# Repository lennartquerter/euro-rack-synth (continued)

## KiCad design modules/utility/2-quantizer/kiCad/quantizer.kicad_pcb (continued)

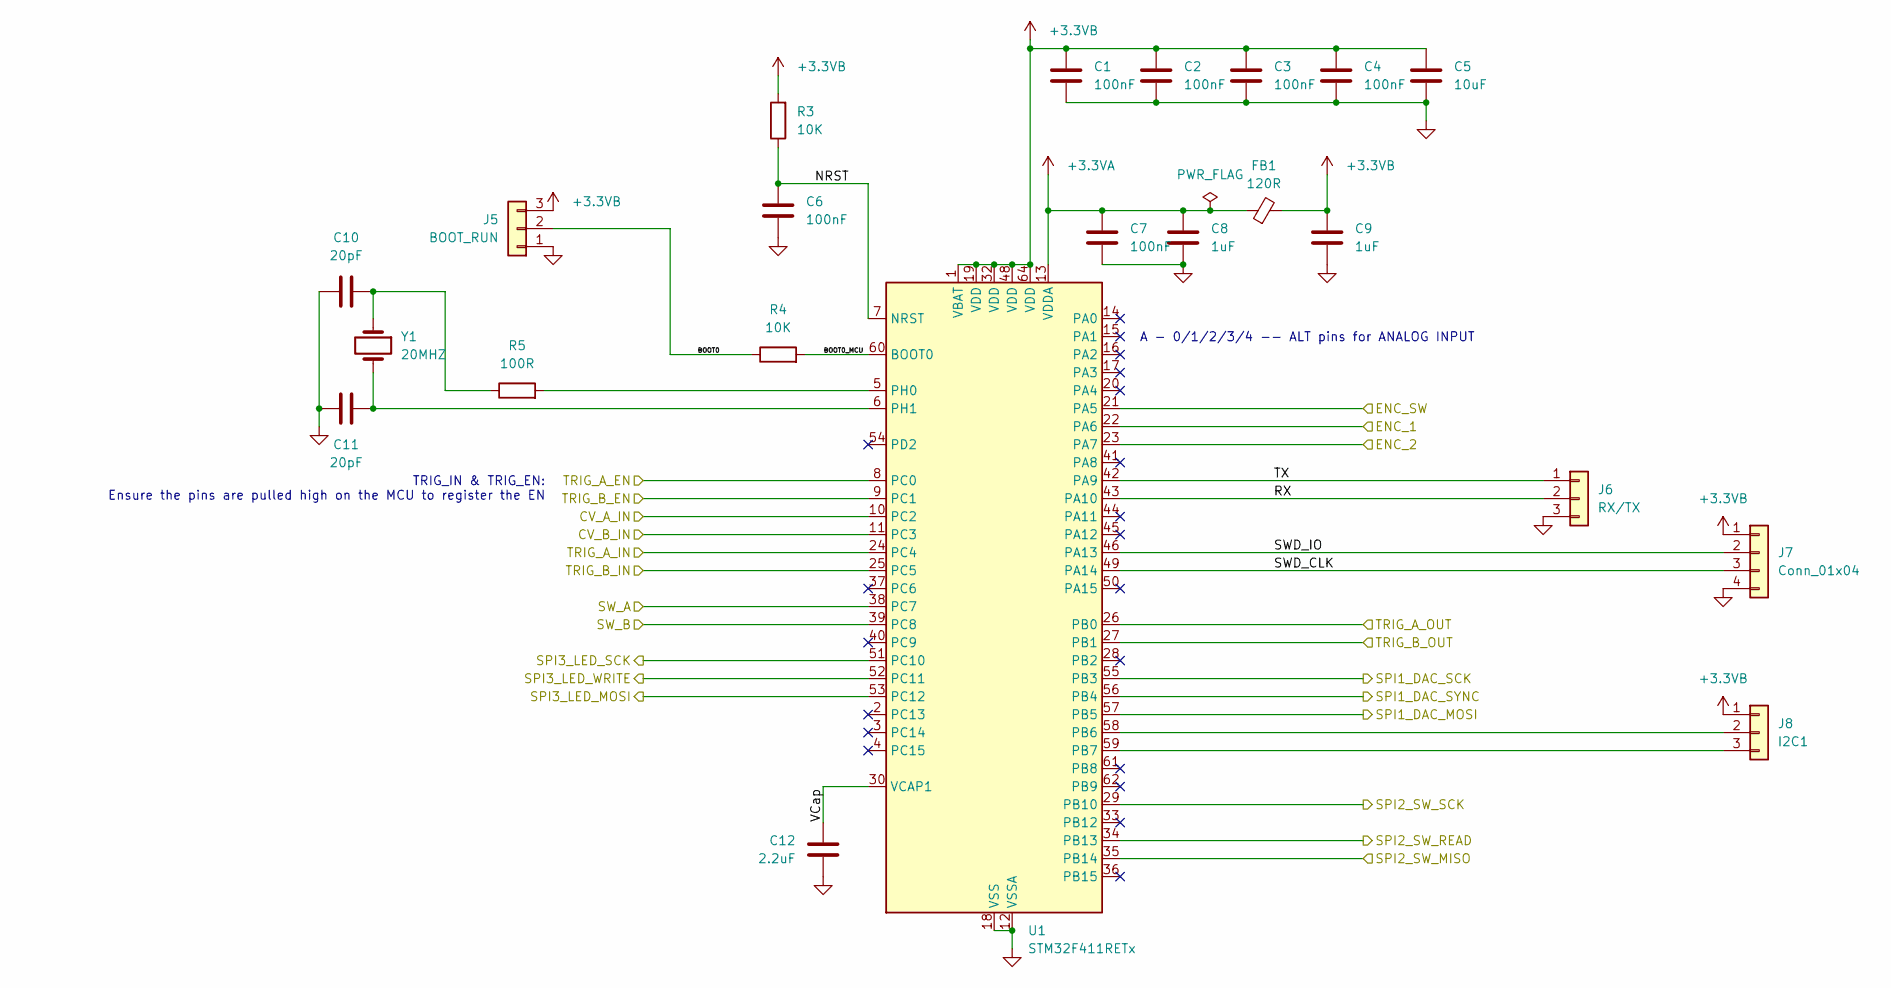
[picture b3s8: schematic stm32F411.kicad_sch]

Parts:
C1, C2, C3, C4, C6, C7: 100nF; C_0805_2012Metric_Pad1.18x1.45mm_HandSolder
C5: 10uF; C_0805_2012Metric_Pad1.18x1.45mm_HandSolder
C8, C9: 1uF; C_0805_2012Metric_Pad1.18x1.45mm_HandSolder
C10, C11: 20pF; C_0805_2012Metric_Pad1.18x1.45mm_HandSolder
C12: 2.2uF; C_0805_2012Metric_Pad1.18x1.45mm_HandSolder
FB1: 120R; L_0805_2012Metric_Pad1.05x1.20mm_HandSolder
J5: BOOT_RUN; PinHeader_1x03_P2.54mm_Vertical
J6: RX/TX; PinHeader_1x03_P2.54mm_Vertical
J7: Conn_01x04; PinHeader_1x04_P2.54mm_Vertical
J8: I2C1; PinHeader_1x03_P2.54mm_Vertical
R3, R4: 10K; R_0805_2012Metric_Pad1.20x1.40mm_HandSolder
R5: 100R; R_0805_2012Metric_Pad1.20x1.40mm_HandSolder
U1: STM32F411RETx; LQFP-64_10x10mm_P0.5mm
Y1: 20MHZ; Crystal_SMD_HC49-SD

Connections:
+3.3VA: C7.2, C8.2, FB1.1, U1.13 (VDDA)
+3.3VB: C1.2, C2.2, C3.2, C4.2, C5.2, C9.2, FB1.2, J5.3, J7.1, J8.1, R3.2, U1.1 (VBAT), U1.19 (VDD), U1.32 (VDD), U1.48 (VDD), U1.64 (VDD); also elsewhere on the board
/cv_normalizer1/CV_OUT: U1.11 (PC3); also elsewhere on the board
/cv_normalizer/CV_OUT: U1.10 (PC2); also elsewhere on the board
/cv_output/SCLK: U1.55 (PB3); also elsewhere on the board
/cv_output/SDIN: U1.57 (PB5); also elsewhere on the board
/cv_output/_SYNC: U1.56 (PB4); also elsewhere on the board
/stm32F411/BOOT0: J5.2, R4.1
/stm32F411/BOOT0_MCU: R4.2, U1.60 (BOOT0)
/stm32F411/ENC_1: U1.22 (PA6); also elsewhere on the board
/stm32F411/ENC_2: U1.23 (PA7); also elsewhere on the board
/stm32F411/ENC_SW: U1.21 (PA5); also elsewhere on the board
/stm32F411/NRST: C6.1, R3.1, U1.7 (NRST)
/stm32F411/RX: J6.2, U1.43 (PA10)
/stm32F411/SPI2_SW_MISO: U1.35 (PB14); also elsewhere on the board
/stm32F411/SPI2_SW_READ: U1.34 (PB13); also elsewhere on the board
/stm32F411/SPI2_SW_SCK: U1.29 (PB10); also elsewhere on the board
/stm32F411/SPI3_LED_MOSI: U1.53 (PC12); also elsewhere on the board
/stm32F411/SPI3_LED_SCK: U1.51 (PC10); also elsewhere on the board
/stm32F411/SPI3_LED_WRITE: U1.52 (PC11); also elsewhere on the board
/stm32F411/SWD_CLK: J7.3, U1.49 (PA14)
/stm32F411/SWD_IO: J7.2, U1.46 (PA13)
/stm32F411/SW_A: U1.38 (PC7); also elsewhere on the board
/stm32F411/SW_B: U1.39 (PC8); also elsewhere on the board
/stm32F411/TRIG_A_EN: U1.8 (PC0); also elsewhere on the board
/stm32F411/TRIG_A_IN: U1.24 (PC4); also elsewhere on the board
/stm32F411/TRIG_A_OUT: U1.26 (PB0); also elsewhere on the board
/stm32F411/TRIG_B_EN: U1.9 (PC1); also elsewhere on the board
/stm32F411/TRIG_B_IN: U1.25 (PC5); also elsewhere on the board
/stm32F411/TRIG_B_OUT: U1.27 (PB1); also elsewhere on the board
/stm32F411/TX: J6.1, U1.42 (PA9)
/stm32F411/VCap: C12.1, U1.30 (VCAP1)
GND: C1.1, C2.1, C3.1, C4.1, C5.1, C6.2, C7.1, C8.1, C9.1, C10.2, C11.2, C12.2, J5.1, J6.3, J7.4, U1.12 (VSSA), U1.18 (VSS), U1.31 (VSS), U1.47 (VSS), U1.63 (VSS); also elsewhere on the board
unnamed: C10.1, R5.1, Y1.1
unnamed: J8.2, U1.58 (PB6)
unnamed: J8.3, U1.59 (PB7)
unnamed: R5.2, U1.5 (PH0)
unnamed: C11.1, U1.6 (PH1), Y1.2

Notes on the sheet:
A - 0/1/2/3/4 -- ALT pins for ANALOG INPUT
TRIG_IN & TRIG_EN: Ensure the pins are pulled high on the MCU to register the EN

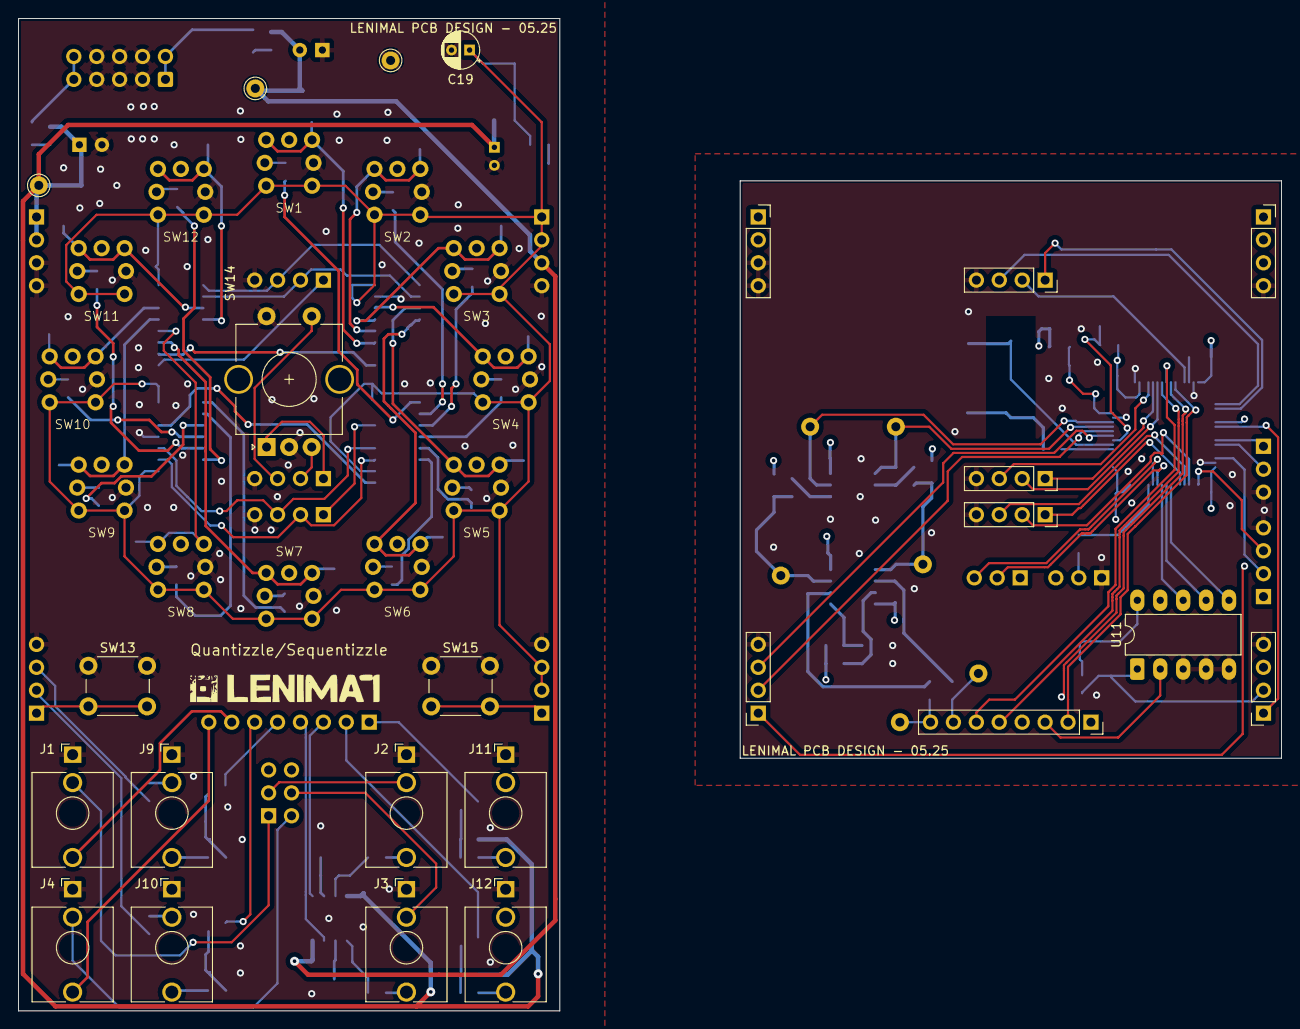
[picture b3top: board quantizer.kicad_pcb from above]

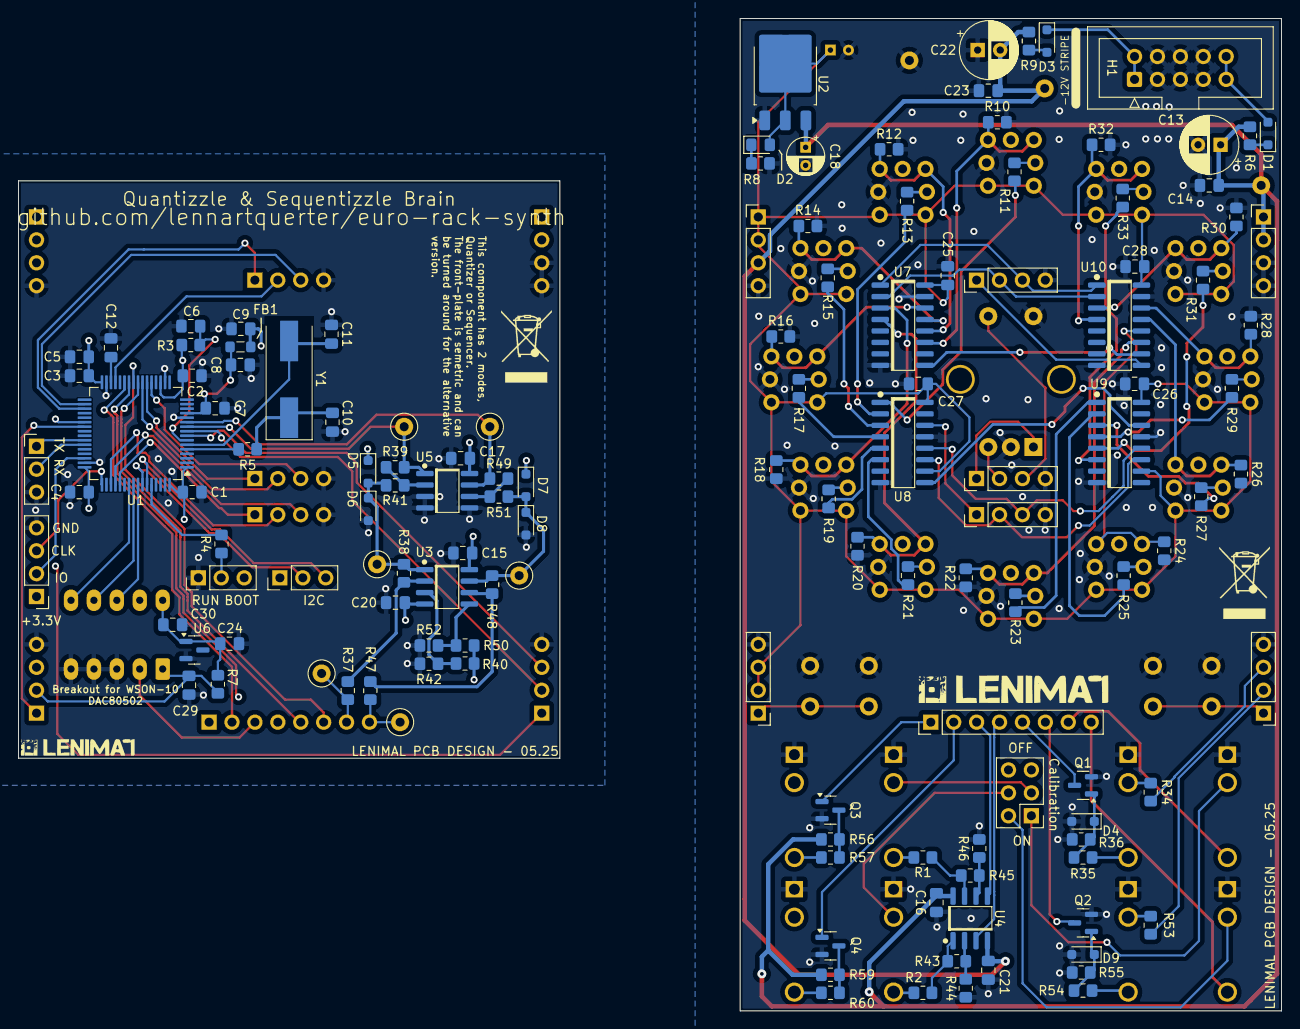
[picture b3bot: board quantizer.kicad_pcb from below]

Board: 4 copper layers, 140.0 x 110.0 mm, 169 parts (133 on the bottom side), 141 nets.

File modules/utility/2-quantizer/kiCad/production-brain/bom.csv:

Designator,Footprint,Quantity,Value,LCSC Part #
"C1, C15, C17, C2, C20, C29, C3, C30, C4, C6, C7",0805,11,100nF,
"C10, C11",0805,2,20pF,
C12,0805,1,2.2uF,
C24,0805,1,470nF,
C5,0805,1,10uF,
"C8, C9",0805,2,1uF,
"D5, D6, D7, D8",D_SOD-323_HandSoldering,4,1N5817,
FB1,0805,1,120R,
J5,PinHeader_1x03_P2.54mm_Vertical,1,BOOT_RUN,
J6,PinHeader_1x03_P2.54mm_Vertical,1,RX/TX,
J7,PinHeader_1x04_P2.54mm_Vertical,1,Conn_01x04,
J8,PinHeader_1x03_P2.54mm_Vertical,1,I2C1,
"R3, R4",0805,2,10K,
"R37, R47",0805,2,40K [0.1%],
"R38, R39, R41, R48, R49, R51",0805,6,10K [0.1%],
"R40, R50",0805,2,22K [1%],
"R42, R52",0805,2,18K [1%],
R5,0805,1,100R,
R7,0805,1,1K,
"TP4, TP7",TestPoint_Loop_D2.50mm_Drill1.0mm,2,CV_IN,
"TP5, TP8",TestPoint_Loop_D2.50mm_Drill1.0mm,2,CV_OUT_1,
"TP6, TP9",TestPoint_Loop_D2.50mm_Drill1.0mm,2,CV_OUT_2,
U1,LQFP-64_10x10mm_P0.5mm,1,STM32F411RETx,
U11,DIP-10_W7.62mm_LongPads,1,DAC80502,
U3,SOIC-8,1,TL072,
U5,SOIC-8,1,MCP6002,
U6,SOT-23,1,LM4040DBZ-2.5,
"XP12, XP14, XP15, XP3, XP6, XP8, XP9",PinSocket_1x04_P2.54mm_Vertical,7,Conn_01x04_Socket,
XP2,PinSocket_1x08_P2.54mm_Vertical,1,Conn_01x08_Socket,
Y1,Crystal_SMD_HC49-SD,1,20MHZ,

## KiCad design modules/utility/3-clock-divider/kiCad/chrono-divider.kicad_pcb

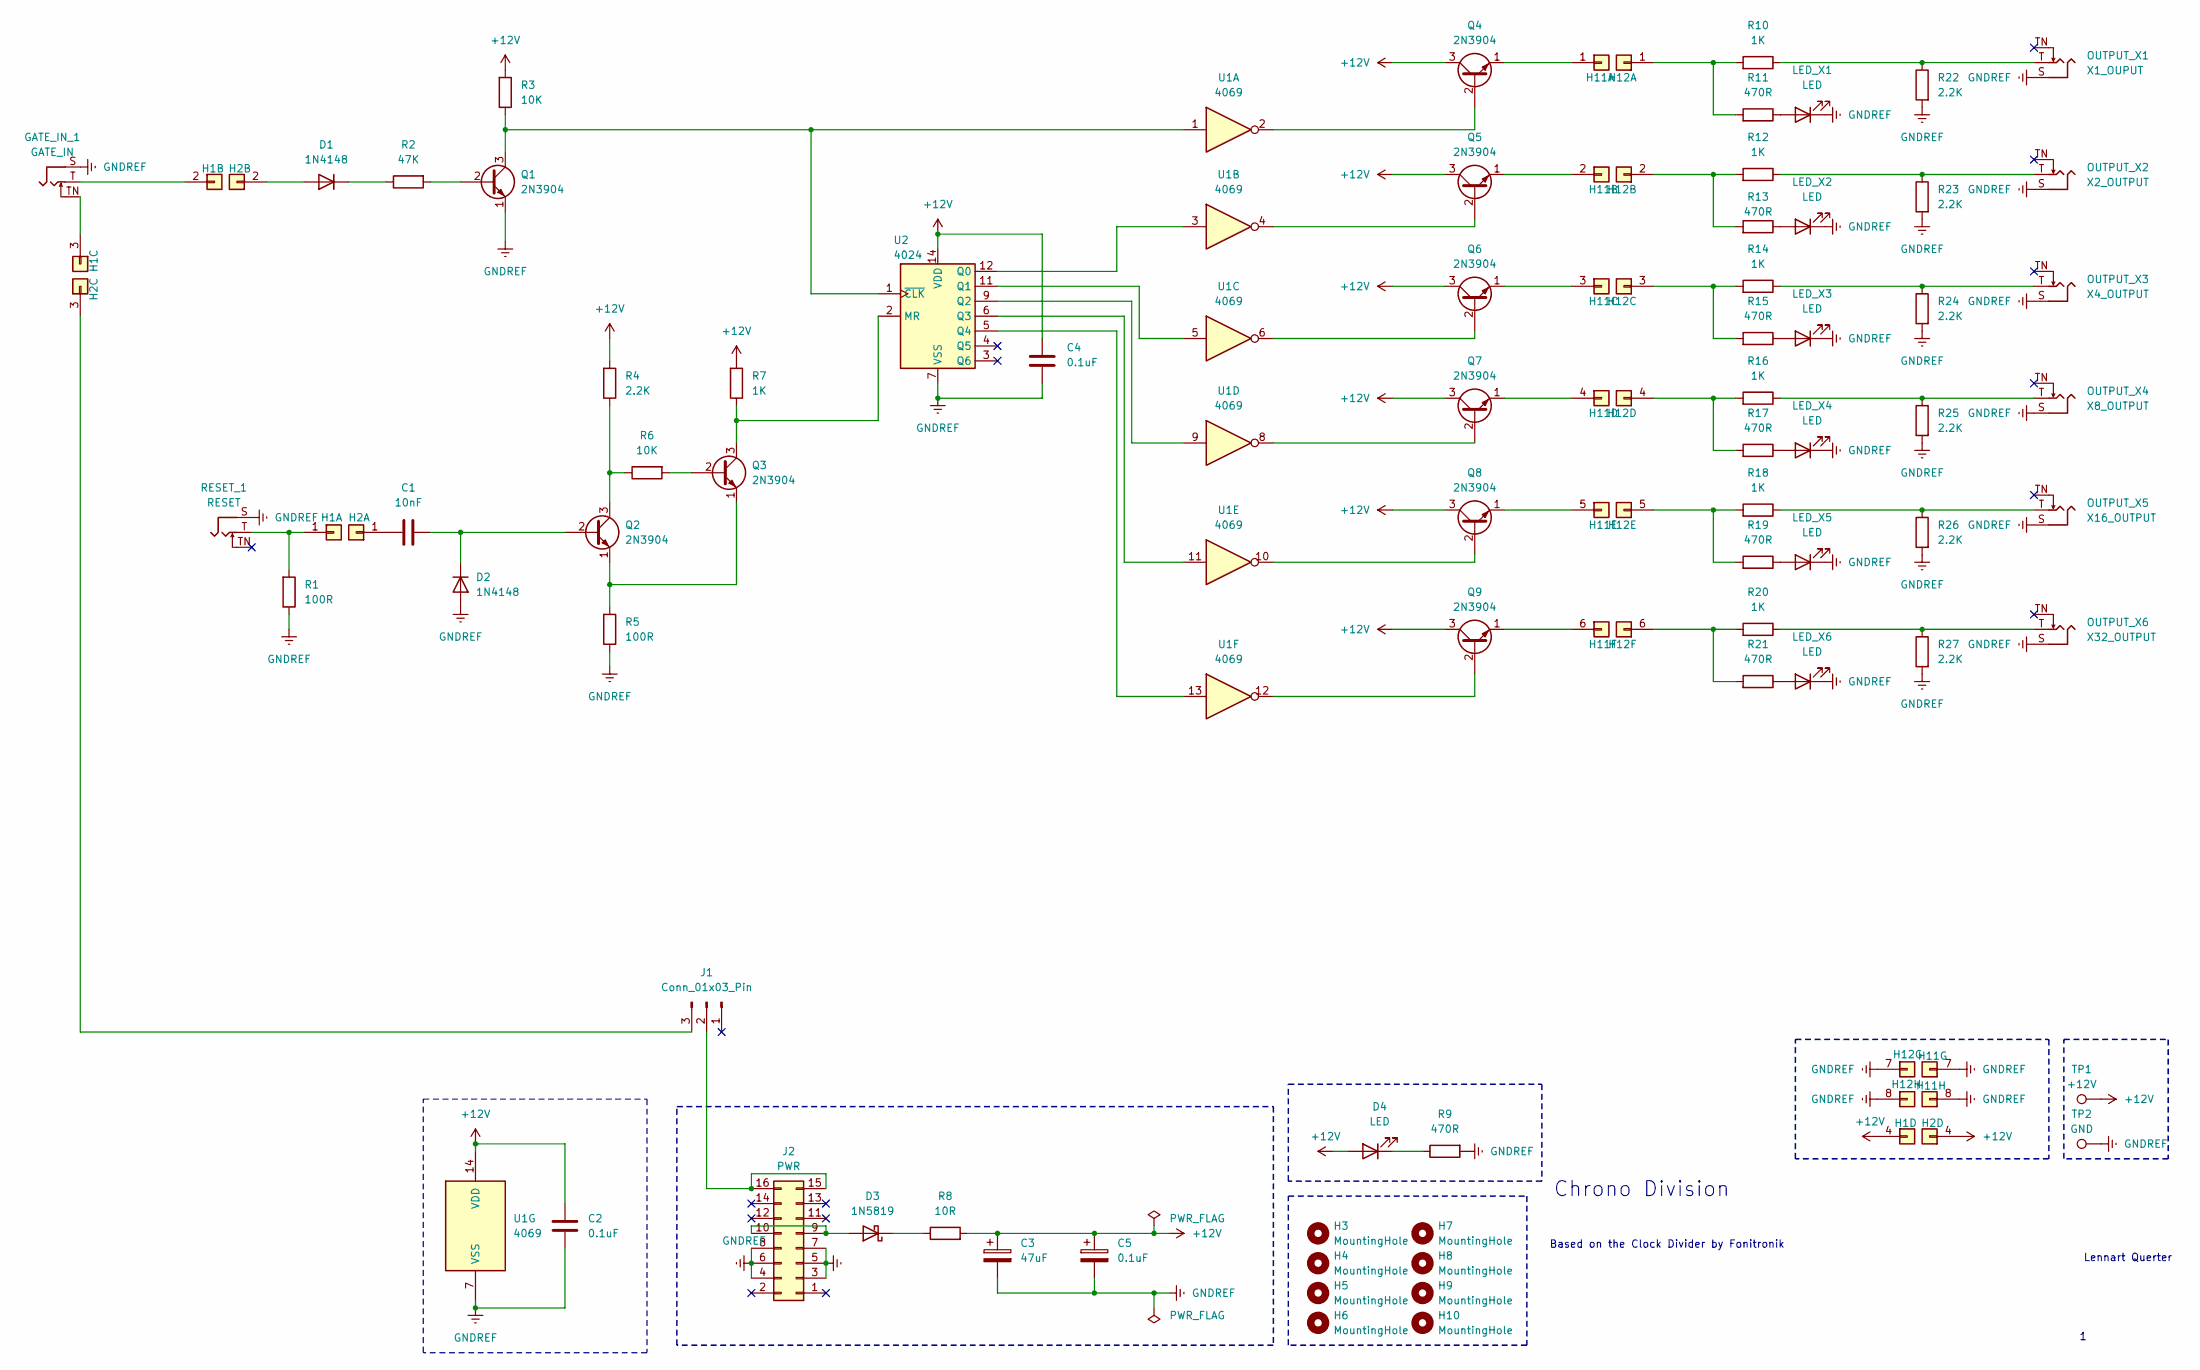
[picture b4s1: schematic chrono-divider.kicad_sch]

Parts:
C1: 10nF; C_RECT_WIMA_0.1uF
C2, C4: 0.1uF; C_Rect_L4.6mm_W2.0mm_P2.50mm_MKS02_FKP02
C3: 47uF; CP_Radial_D6.3mm_P2.50mm
C5: 0.1uF; CP_Radial_D4.0mm_P2.00mm
D1, D2: 1N4148; D_DO-35_SOD27_P7.62mm_Horizontal
D3: 1N5819; D_DO-41_SOD81_P10.16mm_Horizontal
D4: LED; LED_D5.0mm (center Aligned)
GATE_IN_1: GATE_IN; Jack_3.5mm_QingPu_WQP-PJ398SM_Vertical_CircularHoles
H1: H5; PinHeader_1x04_P2.54mm_Vertical
H2: H6; PinSocket_1x04_P2.54mm_Vertical
H3, H4, H5, H6, H7, H8, H9, H10: MountingHole; MountingHole_3.2mm_M3
H11: H4; PinSocket_1x08_P2.54mm_Vertical
H12: H2; PinHeader_1x08_P2.54mm_Vertical
J1: Conn_01x03_Pin; PinHeader_1x03_P2.54mm_Vertical
J2: PWR; IDC-Header_2x08_P2.54mm_Vertical
LED_X1, LED_X2, LED_X3, LED_X4, LED_X5, LED_X6: LED; LED_D5.0mm (center Aligned)
OUTPUT_X1: X1_OUPUT; Jack_3.5mm_QingPu_WQP-PJ398SM_Vertical_CircularHoles
OUTPUT_X2: X2_OUTPUT; Jack_3.5mm_QingPu_WQP-PJ398SM_Vertical_CircularHoles
OUTPUT_X3: X4_OUTPUT; Jack_3.5mm_QingPu_WQP-PJ398SM_Vertical_CircularHoles
OUTPUT_X4: X8_OUTPUT; Jack_3.5mm_QingPu_WQP-PJ398SM_Vertical_CircularHoles
OUTPUT_X5: X16_OUTPUT; Jack_3.5mm_QingPu_WQP-PJ398SM_Vertical_CircularHoles
OUTPUT_X6: X32_OUTPUT; Jack_3.5mm_QingPu_WQP-PJ398SM_Vertical_CircularHoles
Q1, Q2, Q3, Q4, Q5, Q6, Q7, Q8, Q9: 2N3904; TO-92_HandSolder
R1, R5: 100R; R_Default (DIN0207)
R2: 47K; R_Default (DIN0207)
R3, R6: 10K; R_Default (DIN0207)
R4, R22, R23, R24, R25, R26, R27: 2.2K; R_Default (DIN0207)
R7, R10, R12, R14, R16, R18, R20: 1K; R_Default (DIN0207)
R8: 10R; R_Default (DIN0207)
R9, R11, R13, R15, R17, R19, R21: 470R; R_Default (DIN0207)
RESET_1: RESET; Jack_3.5mm_QingPu_WQP-PJ398SM_Vertical_CircularHoles
TP1: +12V; Pin_D1.0mm_L10.0mm
TP2: GND; Pin_D1.0mm_L10.0mm
U1: 4069; DIP-14_W7.62mm_Socket_LongPads
U2: 4024; DIP-14_W7.62mm_Socket_LongPads

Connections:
+12V: C2.1, C3.1, C4.1, C5.1, D4.2 (A), H1.4, H2.4, Q4.3 (C), Q5.3 (C), Q6.3 (C), Q7.3 (C), Q8.3 (C), Q9.3 (C), R3.1, R4.1, R7.1, R8.2, TP1.1, U1.14 (VDD), U2.14 (VDD)
GNDREF: C2.2, C3.2, C4.2, C5.2, D2.2 (A), GATE_IN_1.S, H11.7, H11.8, H12.7, H12.8, J2.3 (GND), J2.4 (GND), J2.5 (GND), J2.6 (GND), J2.7 (GND), J2.8 (GND), LED_X1.1 (K), LED_X2.1 (K), LED_X3.1 (K), LED_X4.1 (K), LED_X5.1 (K), LED_X6.1 (K), OUTPUT_X1.S, OUTPUT_X2.S, OUTPUT_X3.S, OUTPUT_X4.S, OUTPUT_X5.S, OUTPUT_X6.S, Q1.1 (E), R1.2, R5.2, R9.1, R22.1, R23.1, R24.1, R25.1, R26.1, R27.1, RESET_1.S, TP2.1, U1.7 (VSS), U2.7 (VSS)
unnamed: D1.2 (A), H2.2
unnamed: D1.1 (K), R2.2
unnamed: C1.2, D2.1 (K), Q2.2 (B)
unnamed: D3.2 (A), J2.9 (+12V), J2.10 (+12V)
unnamed: D3.1 (K), R8.1
unnamed: D4.1 (K), R9.2
unnamed: H1.1, R1.1, RESET_1.T
unnamed: GATE_IN_1.T, H1.2
unnamed: GATE_IN_1.TN, H1.3
unnamed: C1.1, H2.1
unnamed: H2.3, J1.3
unnamed: H11.1 (Pin_3), Q4.1 (E)
unnamed: H11.2, Q5.1 (E)
unnamed: H11.3, Q6.1 (E)
unnamed: H11.4, Q7.1 (E)
unnamed: H11.5, Q8.1 (E)
unnamed: H11.6, Q9.1 (E)
unnamed: H12.1, R10.1, R11.1
unnamed: H12.2, R12.1, R13.1
unnamed: H12.3, R14.1, R15.1
unnamed: H12.4, R16.1, R17.1
unnamed: H12.5, R18.1, R19.1
unnamed: H12.6, R20.1, R21.1
unnamed: J1.2, J2.15 (GATE), J2.16 (GATE)
unnamed: LED_X1.2 (A), R11.2
unnamed: LED_X2.2 (A), R13.2
unnamed: LED_X3.2 (A), R15.2
unnamed: LED_X4.2 (A), R17.2
unnamed: LED_X5.2 (A), R19.2
unnamed: LED_X6.2 (A), R21.2
unnamed: OUTPUT_X1.T, R10.2, R22.2
unnamed: OUTPUT_X2.T, R12.2, R23.2
unnamed: OUTPUT_X3.T, R14.2, R24.2
unnamed: OUTPUT_X4.T, R16.2, R25.2
unnamed: OUTPUT_X5.T, R18.2, R26.2
unnamed: OUTPUT_X6.T, R20.2, R27.2
unnamed: Q1.2 (B), R2.1
unnamed: Q1.3 (C), R3.2, U1.1, U2.1 (~CLK)
unnamed: Q2.3 (C), R4.2, R6.2
unnamed: Q2.1 (E), Q3.1 (E), R5.1
unnamed: Q3.2 (B), R6.1
unnamed: Q3.3 (C), R7.2, U2.2 (MR)
unnamed: Q4.2 (B), U1.2
unnamed: Q5.2 (B), U1.4
unnamed: Q6.2 (B), U1.6
unnamed: Q7.2 (B), U1.8
unnamed: Q8.2 (B), U1.10
unnamed: Q9.2 (B), U1.12
unnamed: U1.3, U2.12 (Q0)
unnamed: U1.5, U2.11 (Q1)
unnamed: U1.9, U2.9 (Q2)
unnamed: U1.11, U2.6 (Q3)
unnamed: U1.13, U2.5 (Q4)

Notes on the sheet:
Based on the Clock Divider by Fonitronik
Chrono Division
Lennart Querter

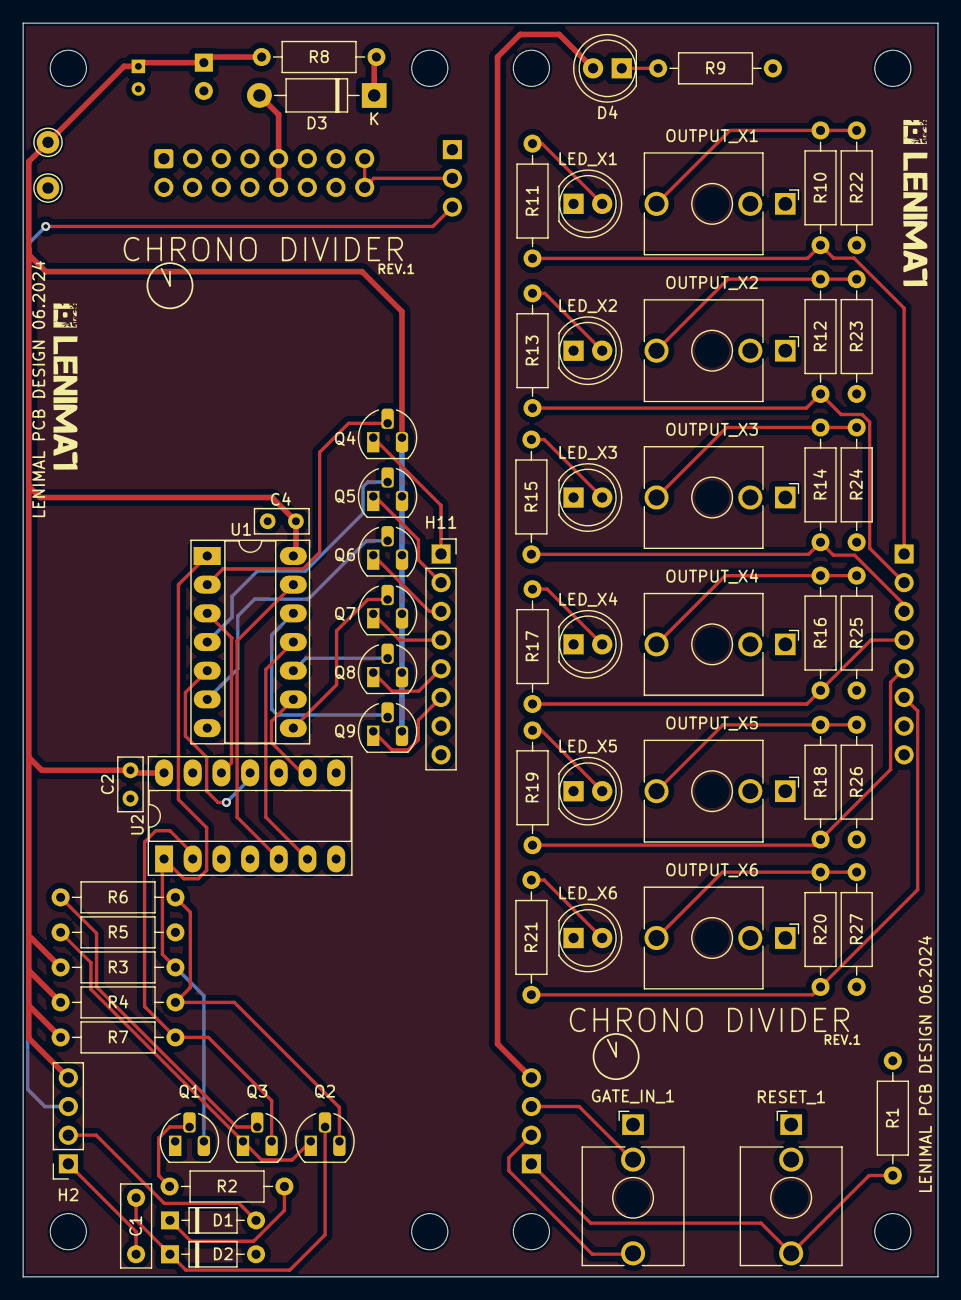
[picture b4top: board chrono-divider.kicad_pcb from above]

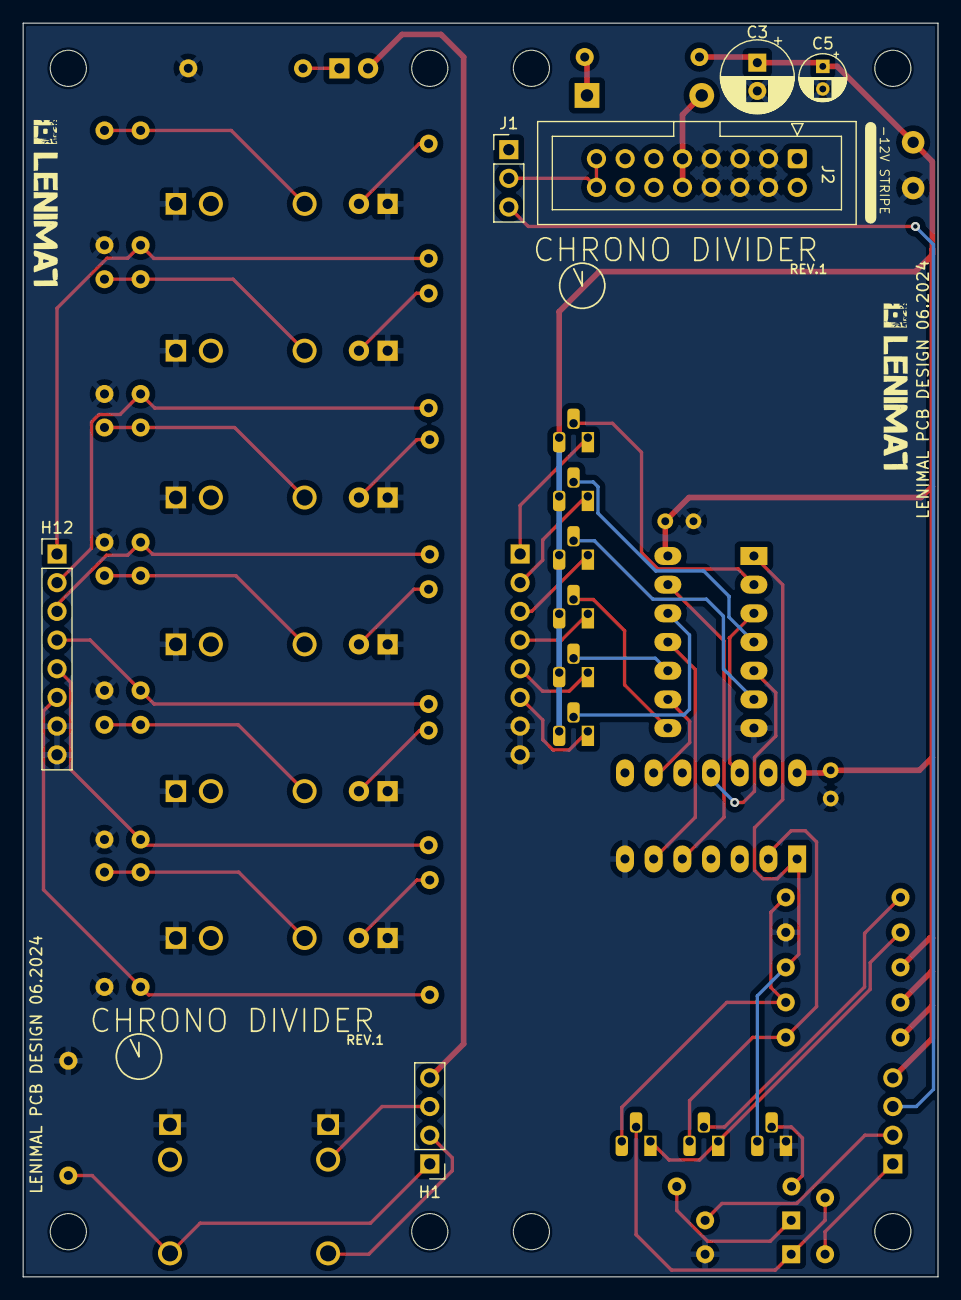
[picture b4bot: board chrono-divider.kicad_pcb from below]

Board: 2 copper layers, 81.0 x 111.0 mm, 77 parts (6 on the bottom side), 55 nets.

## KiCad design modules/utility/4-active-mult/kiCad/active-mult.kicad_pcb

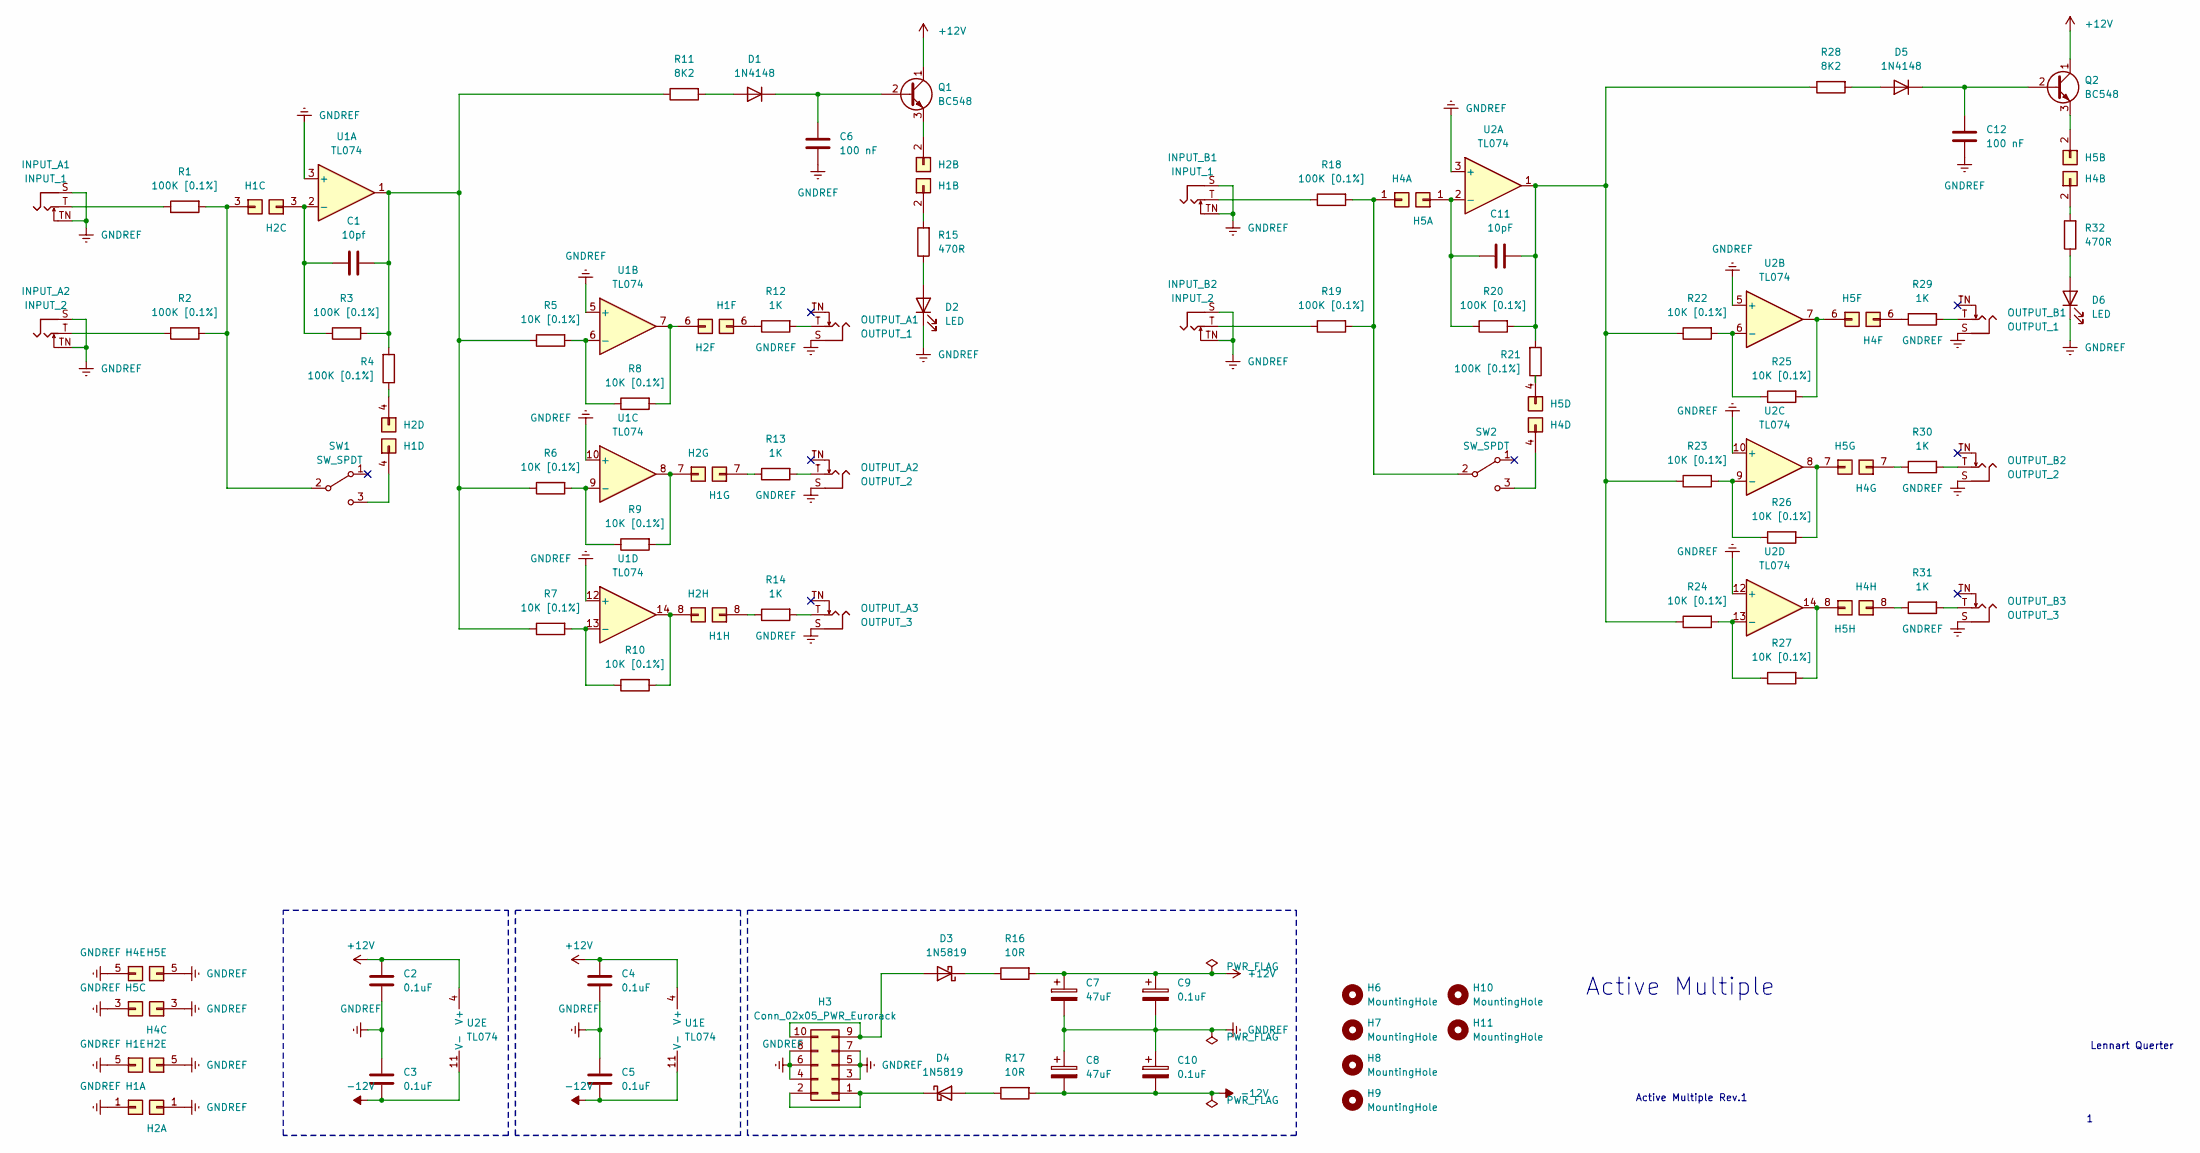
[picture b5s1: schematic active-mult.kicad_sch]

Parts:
C1: 10pf; C_RECT_WIMA_0.1uF
C2, C3, C4, C5: 0.1uF; C_Disc_D5.0mm_W2.5mm_P5.00mm
C6, C12: 100 nF; C_RECT_WIMA_0.1uF
C7, C8: 47uF; CP_Radial_D6.3mm_P2.50mm
C9, C10: 0.1uF; CP_Radial_D4.0mm_P2.00mm
C11: 10pF; C_RECT_WIMA_0.1uF
D1, D5: 1N4148; D_DO-35_SOD27_P7.62mm_Horizontal
D2, D6: LED; LED_D5.0mm (center Aligned)
D3, D4: 1N5819; D_DO-41_SOD81_P10.16mm_Horizontal
H1, H4: PinHeader_1x08; PinHeader_1x08_P2.54mm_Vertical
H2, H5: PinSocket_1x08; PinSocket_1x08_P2.54mm_Vertical
H3: Conn_02x05_PWR_Eurorack; IDC-Header_2x05_P2.54mm_Vertical
H6, H7, H8, H9, H10, H11: MountingHole; MountingHole_3.2mm_M3
INPUT_A1: INPUT_1; Jack_3.5mm_QingPu_WQP-PJ398SM_Vertical_CircularHoles
INPUT_A2: INPUT_2; Jack_3.5mm_QingPu_WQP-PJ398SM_Vertical_CircularHoles
INPUT_B1: INPUT_1; Jack_3.5mm_QingPu_WQP-PJ398SM_Vertical_CircularHoles
INPUT_B2: INPUT_2; Jack_3.5mm_QingPu_WQP-PJ398SM_Vertical_CircularHoles
OUTPUT_A1: OUTPUT_1; Jack_3.5mm_QingPu_WQP-PJ398SM_Vertical_CircularHoles
OUTPUT_A2: OUTPUT_2; Jack_3.5mm_QingPu_WQP-PJ398SM_Vertical_CircularHoles
OUTPUT_A3: OUTPUT_3; Jack_3.5mm_QingPu_WQP-PJ398SM_Vertical_CircularHoles
OUTPUT_B1: OUTPUT_1; Jack_3.5mm_QingPu_WQP-PJ398SM_Vertical_CircularHoles
OUTPUT_B2: OUTPUT_2; Jack_3.5mm_QingPu_WQP-PJ398SM_Vertical_CircularHoles
OUTPUT_B3: OUTPUT_3; Jack_3.5mm_QingPu_WQP-PJ398SM_Vertical_CircularHoles
Q1, Q2: BC548; TO-92_HandSolder
R1, R2, R3, R4, R18, R19, R20, R21: 100K [0.1%]; R_Default (DIN0207)
R5, R6, R7, R8, R9, R10, R22, R23, R24, R25, R26, R27: 10K [0.1%]; R_Default (DIN0207)
R11, R28: 8K2; R_Default (DIN0207)
R12, R13, R14, R29, R30, R31: 1K; R_Default (DIN0207)
R15, R32: 470R; R_Default (DIN0207)
R16, R17: 10R; R_Default (DIN0207)
SW1, SW2: SW_SPDT; SW_default
U1, U2: TL074; DIP-14_W7.62mm_Socket_LongPads

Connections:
+12V: C2.1, C4.1, C7.1, C9.1, Q1.1 (C), Q2.1 (C), R16.1, U1.4 (V+), U2.4 (V+)
-12V: C3.2, C5.2, C8.2, C10.2, R17.1, U1.11 (V-), U2.11 (V-)
GNDREF: C2.2, C3.1, C4.2, C5.1, C6.1, C7.2, C8.1, C9.2, C10.1, C12.1, D2.1 (K), D6.1 (K), H1.1, H1.5, H2.1 (Pin_3), H2.5, H3.3, H3.4, H3.5, H3.6, H3.7, H3.8, H4.3, H4.5, H5.3, H5.5, INPUT_A1.S, INPUT_A1.TN, INPUT_A2.S, INPUT_A2.TN, INPUT_B1.S, INPUT_B1.TN, INPUT_B2.S, INPUT_B2.TN, OUTPUT_A1.S, OUTPUT_A2.S, OUTPUT_A3.S, OUTPUT_B1.S, OUTPUT_B2.S, OUTPUT_B3.S, U1.3 (+), U1.5 (+), U1.10 (+), U1.12 (+), U2.3 (+), U2.5 (+), U2.10 (+), U2.12 (+)
unnamed: C1.2, R3.1, R4.1, R5.2, R6.2, R7.2, R11.2, U1.1
unnamed: C11.2, R20.1, R21.1, R22.2, R23.2, R24.2, R28.2, U2.1
unnamed: D1.2 (A), R11.1
unnamed: C6.2, D1.1 (K), Q1.2 (B)
unnamed: D2.2 (A), R15.1
unnamed: D3.2 (A), H3.9, H3.10
unnamed: D3.1 (K), R16.2
unnamed: D4.2 (A), R17.2
unnamed: D4.1 (K), H3.1, H3.2
unnamed: D5.2 (A), R28.1
unnamed: C12.2, D5.1 (K), Q2.2 (B)
unnamed: D6.2 (A), R32.1
unnamed: H1.2, R15.2
unnamed: H1.3, R1.1, R2.1, SW1.2 (B)
unnamed: H1.4, SW1.3 (C)
unnamed: H1.6, R12.2
unnamed: H1.7, R13.2
unnamed: H1.8, R14.2
unnamed: H2.2, Q1.3 (E)
unnamed: C1.1, H2.3, R3.2, U1.2 (-)
unnamed: H2.4, R4.2
unnamed: H2.6, R8.1, U1.7
unnamed: H2.7, R9.1, U1.8
unnamed: H2.8, R10.1, U1.14
unnamed: H4.1, R18.1, R19.1, SW2.2 (B)
unnamed: H4.2, R32.2
unnamed: H4.4, SW2.3 (C)
unnamed: H4.6, R29.2
unnamed: H4.7, R30.2
unnamed: H4.8, R31.2
unnamed: C11.1, H5.1 (Pin_3), R20.2, U2.2 (-)
unnamed: H5.2, Q2.3 (E)
unnamed: H5.4, R21.2
unnamed: H5.6, R25.1, U2.7
unnamed: H5.7, R26.1, U2.8
unnamed: H5.8, R27.1, U2.14
unnamed: INPUT_A1.T, R1.2
unnamed: INPUT_A2.T, R2.2
unnamed: INPUT_B1.T, R18.2
unnamed: INPUT_B2.T, R19.2
unnamed: OUTPUT_A1.T, R12.1
unnamed: OUTPUT_A2.T, R13.1
unnamed: OUTPUT_A3.T, R14.1
unnamed: OUTPUT_B1.T, R29.1
unnamed: OUTPUT_B2.T, R30.1
unnamed: OUTPUT_B3.T, R31.1
unnamed: R5.1, R8.2, U1.6 (-)
unnamed: R6.1, R9.2, U1.9 (-)
unnamed: R7.1, R10.2, U1.13 (-)
unnamed: R22.1, R25.2, U2.6 (-)
unnamed: R23.1, R26.2, U2.9 (-)
unnamed: R24.1, R27.2, U2.13 (-)

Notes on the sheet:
Active Multiple Rev.1
Lennart Querter
Active Multiple

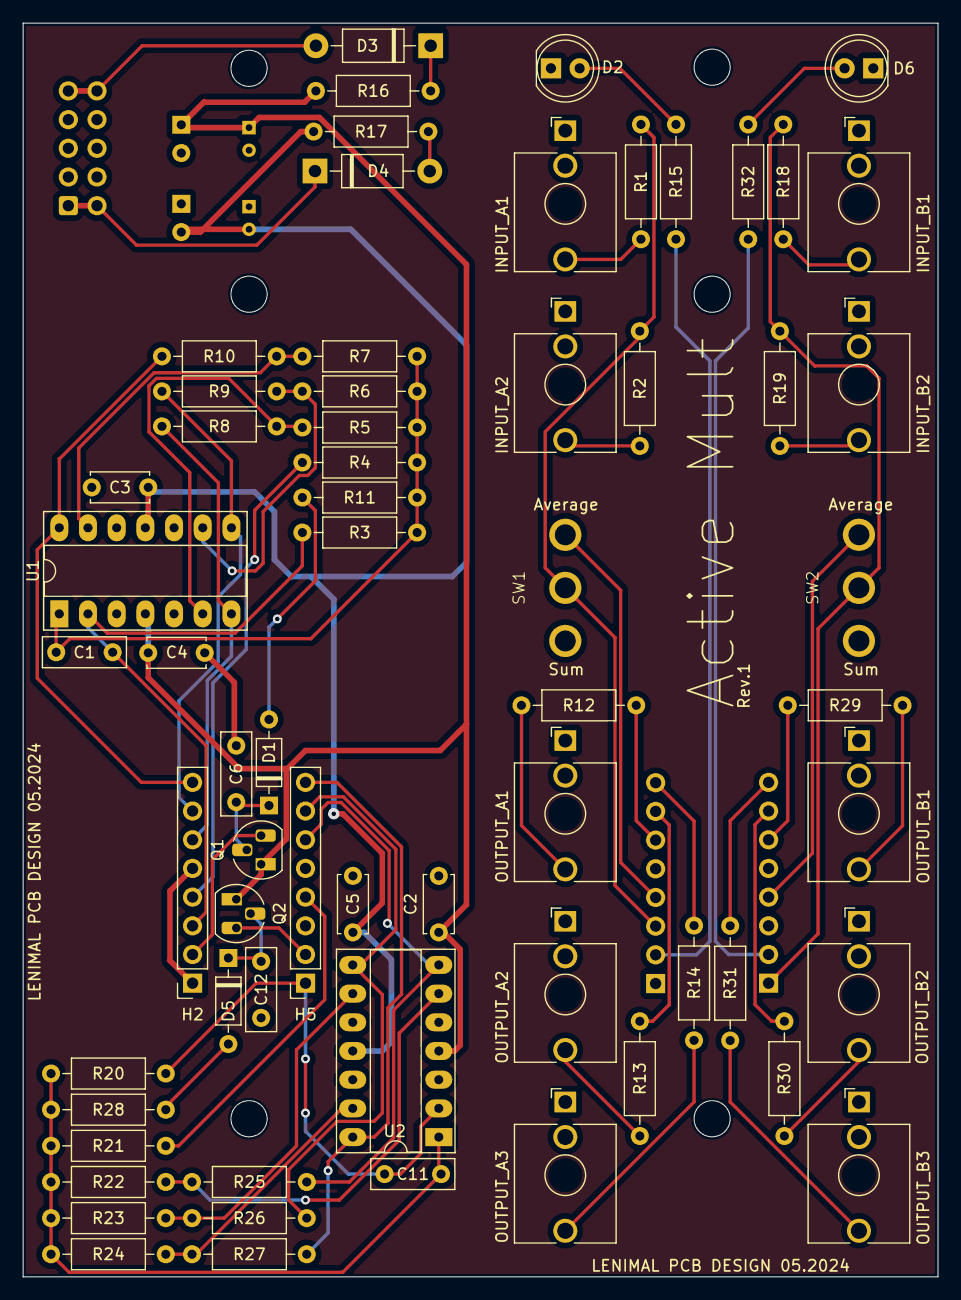
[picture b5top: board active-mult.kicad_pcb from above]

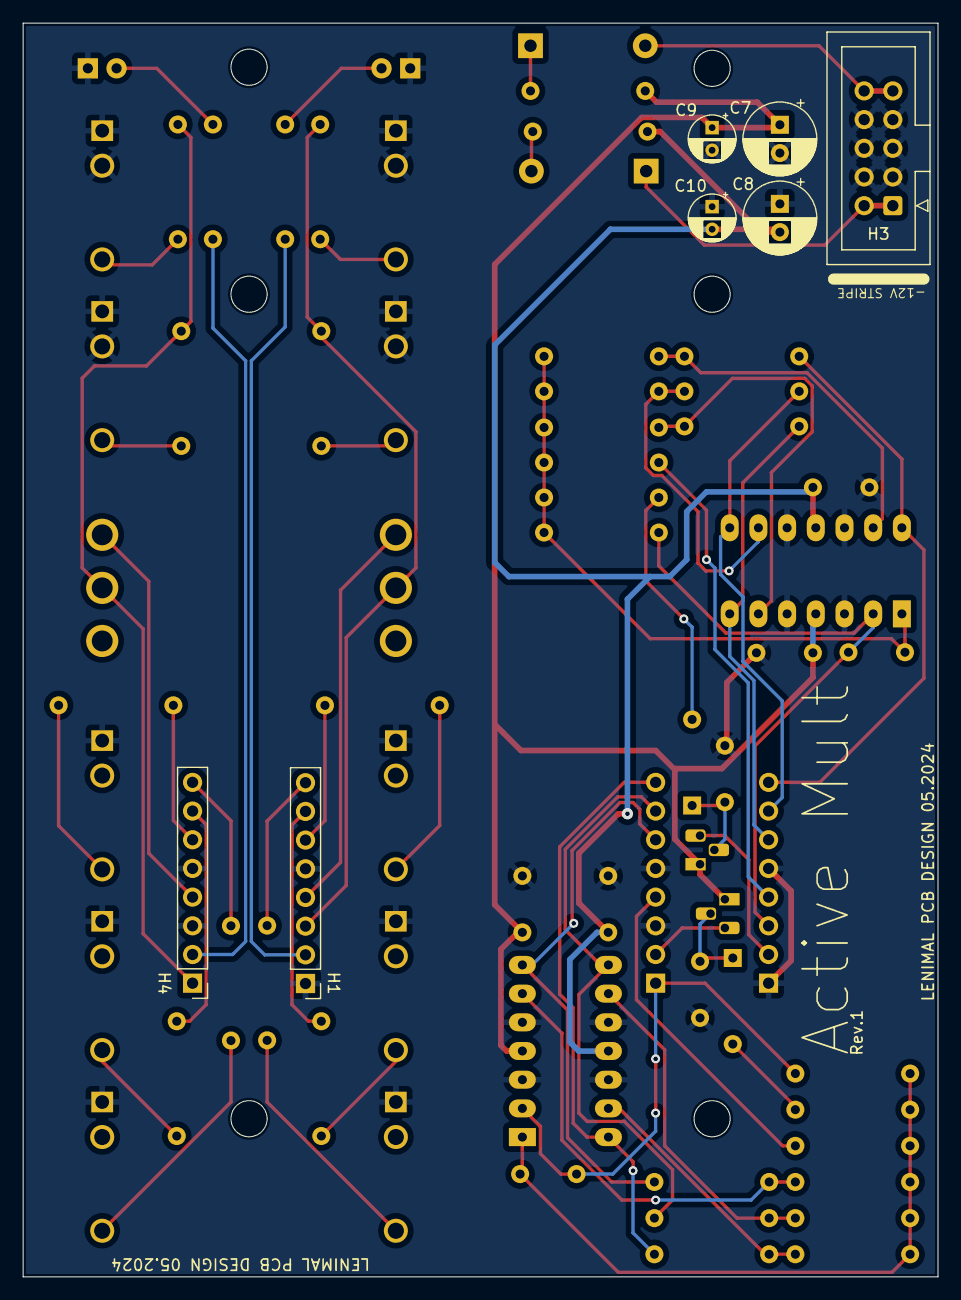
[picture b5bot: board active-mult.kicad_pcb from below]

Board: 2 copper layers, 81.0 x 111.0 mm, 77 parts (7 on the bottom side), 55 nets.
